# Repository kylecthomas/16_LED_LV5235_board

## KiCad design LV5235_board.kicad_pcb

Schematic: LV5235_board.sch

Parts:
C1, C4: 1u; C_0805_HandSoldering
C2, C5: .1u; C_0805_HandSoldering
C3: 100p; C_0805_HandSoldering
GND1, GND2: GND; PINTST
JP1: JUMPER; PINHEAD1-2
R1, R2, R3, R4, R5, R6, R7, R8, R9, R10, R11, R12, R13, R14, R15, R16: 43; R_0805_HandSoldering
R17, R18: 2K; R_0805_HandSoldering
R100: 22K; R_0805_HandSoldering
SCL1: SCL; PINTST
SDA1: SDA; PINTST
SW1: SP3T; CLSB13B02T
U1, U2, U3, U4, U5, U6, U7, U8, U9, U10, U11, U12, U13, U14, U15, U16: OSRAM__LW_E6SG; E6SG
U100: LV5235
V5L1: V5L; PINTST
VDD1: VDD; PINTST

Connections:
+5V: C1.1, C2.1, R17.1, R18.1, SW1.4, U100.1 (SVcc), U100.37 (CTLSCT), U100.40 (RESET), VDD1.1
+5VL: JP1.1, V5L1.1
/LEDB1: R13.2, U100.28 (LEDB1)
/LEDB2: R14.2, U100.29 (LEDB2)
/LEDB3: R15.2, U100.30 (LEDB3)
/LEDB4: R16.2, U100.31 (LEDB4)
/LEDG1: R8.2, U100.14 (LEDG1)
/LEDG2: R5.2, U100.15 (LEDG2)
/LEDG3: R12.2, U100.16 (LEDG3)
/LEDG4: R9.2, U100.17 (LEDG4)
/LEDG5: R11.2, U100.19 (LEDG5)
/LEDG6: R10.2, U100.20 (LEDG6)
/LEDR1: R1.2, U100.5 (LEDR1)
/LEDR2: R2.2, U100.6 (LEDR2)
/LEDR3: R3.2, U100.7 (LEDR3)
/LEDR4: R4.2, U100.8 (LEDR4)
/LEDR5: R7.2, U100.10 (LEDR5)
/LEDR6: R6.2, U100.11 (LEDR6)
/VDD5LJ: C4.1, C5.1, JP1.2, U1.1, U2.1, U3.1, U4.1, U5.1, U6.1, U7.1, U8.1, U9.1, U10.1, U11.1, U12.1, U13.1, U14.1, U15.1, U16.1
GND: C1.2, C2.2, C3.2, C4.2, C5.2, GND1.1, GND2.1, R100.2, SW1.1, U100.4 (SDEN), U100.9 (PGND1), U100.18 (PGND2), U100.23 (A0), U100.24 (A1), U100.25 (A2), U100.26 (A3), U100.27 (A4), U100.32 (PGND3), U100.38 (SGND), U100.39 (TEST)
unnamed: C3.1, U100.42 (CT)
unnamed: R1.1, U1.2
unnamed: R2.1, U2.2
unnamed: R3.1, U3.2
unnamed: R4.1, U4.2
unnamed: R5.1, U5.2
unnamed: R6.1, U6.2
unnamed: R7.1, U7.2
unnamed: R8.1, U8.2
unnamed: R9.1, U9.2
unnamed: R10.1, U10.2
unnamed: R11.1, U11.2
unnamed: R12.1, U12.2
unnamed: R13.1, U13.2
unnamed: R14.1, U14.2
unnamed: R15.1, U15.2
unnamed: R16.1, U16.2
unnamed: R17.2, SDA1.1, U100.3 (SDATA)
unnamed: R18.2, SCL1.1, U100.2 (SCLK)
unnamed: R100.1, U100.41 (RT1)
unnamed: SW1.3, U100.43 (OUTSCT)

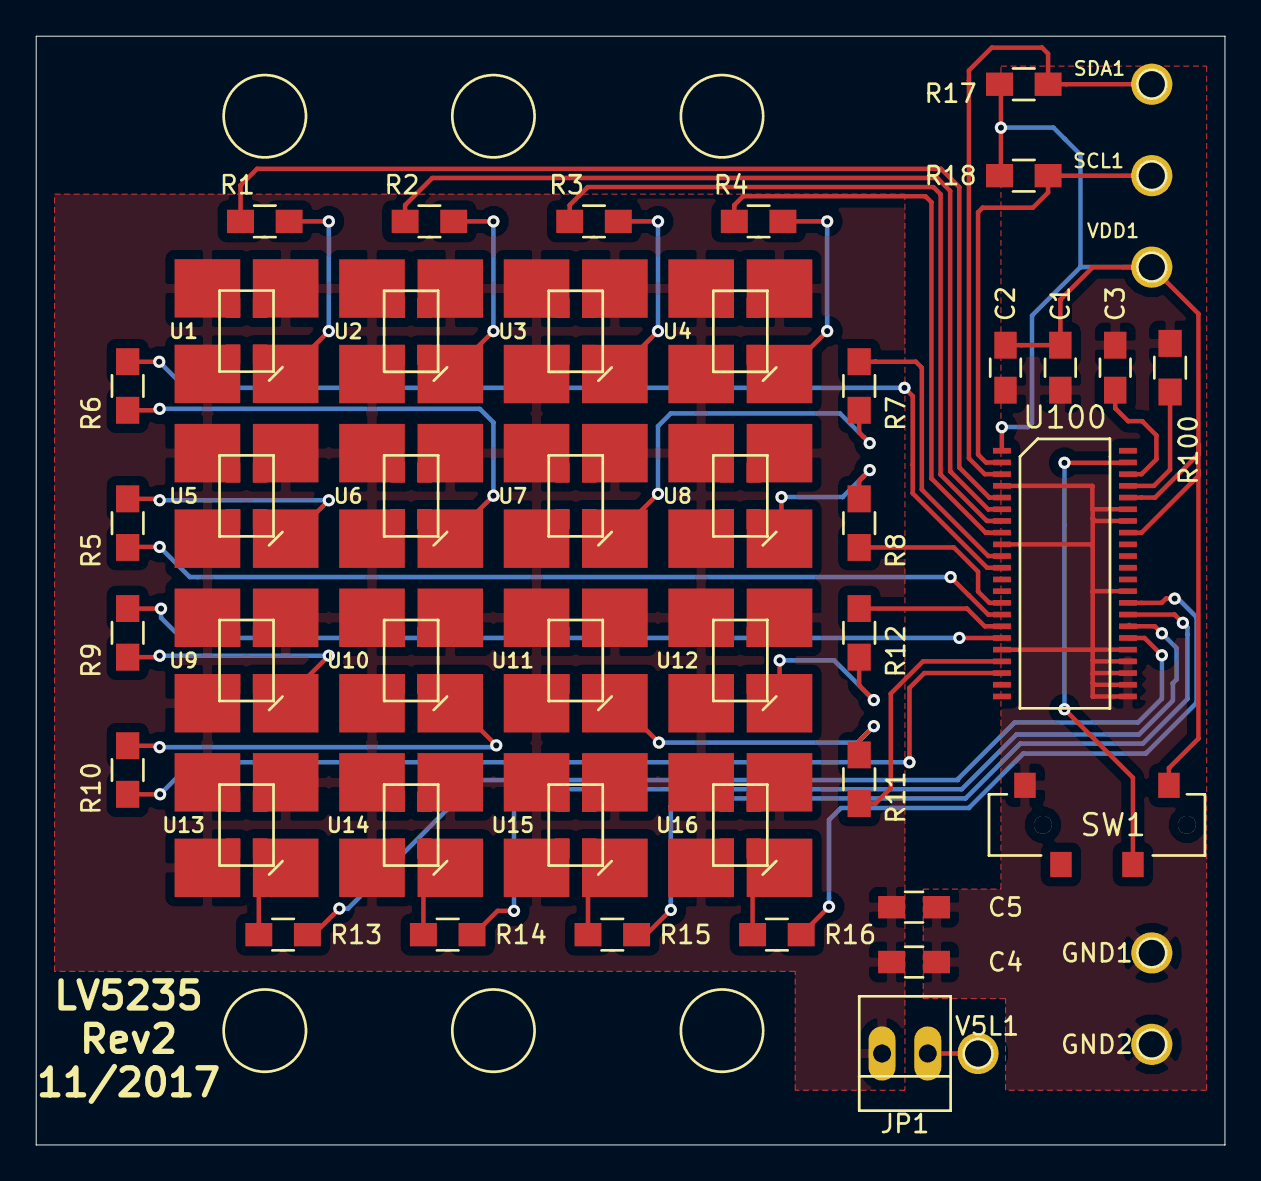
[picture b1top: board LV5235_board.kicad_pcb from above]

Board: 2 copper layers, 66.0 x 61.6 mm, 49 parts (0 on the bottom side), 41 nets.

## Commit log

2017-11-27 Initial Commit
    Initial Commit
